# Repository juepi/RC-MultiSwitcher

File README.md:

# RC-MultiSwitcher
Hard- and software project to handle several RC (PWM) Servo In- and outputs as well as switched Outputs for LEDs and other loads.

## Purpose
My intention for this project was to be able to use a single RC channel for multiple purposes, like switching headlights, flashing lights, siren etc on my RC model. To be more flexible, the board provides 4 PWM servo inputs as well as 4 outputs, which can be used simultaneously. It additionally supports 6 N-channel MOSFET outputs, supporting an optional free-wheeling diode for inductive loads on every output.

## Requirements
Whilst the program has been tested and runs on an Nano 3.0 clone, you may want to use something stronger like a [Teensy 3.1+ board](https://www.pjrc.com/teensy/teensy31.html) for this. The Nano causes some jitter on the servo outputs, i assume due to the interrupts used to measure the PWM signal of the 2 servo input channels interfering with the servo library code.  
If you choose a different microcontroller, my recommendation is to make sure that it is 5V tolerant on the digital inputs (just to be sure). Also remenber that you'll require inputs that support interrupts for decoding the receivers PWM signals.

## Status
This is work in progress, the current code is a POC on decoding the 2 RC channels along with servo output. Still much work to do adding the functionality i want and also a PCB to hook things up to.  
Some documentation available in comments which should help you get things up and running.  
**Update 2022-02-08:** Implemented support for Teensy 3.1/3.2 boards, Servo output jitter is history now!  
**Update 2022-02-11:** Added KiCAD project with schematic and layout for Teensy 3.1+ based MCU. KiCAD project is finished so far, will add gerber data as soon as i've finished the first order at JLCPCB.  
**Update 2022-02-14:** KiCAD project finished after some minor layout improvements. Added gerber, drilling, placement files as well as BoM in "production" subfolder.  
**Update 2022-02-24:** Implemented minor changes on PCB (v1.1): added possibility to provide power via 2pin JST XH plug; added solder-pad to short-circuit fuse (use with caution!); updated manufacturing files  
**Updated 2022-03-04:** Ordered PCB just arrived (v1.0) and works perfectly well! Not yet tested: high power load and PWM output on MOSFET switches.  

## Usage

have fun,  
Juergen

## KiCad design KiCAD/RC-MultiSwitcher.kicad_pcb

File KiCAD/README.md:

# RC-MultiSwitcher
Hardware part of the project. Designed using KiCAD6, SMT parts used from the [JLCPCB parts list](https://jlcpcb.com/parts) to allow pre-assembling all the SMT parts.

## Purpose
Provide power to teensy MCU from BEC (up to 7.2V, Servo input 1) using LDO regulator provide hardware connections for Servo in- and outputs as wells as 6 N-channel MOSFET switched outputs (all 6 support PWM). The PCB has a 5A polyfuse installed at the power input to avoid overload (however, you will still have to make sure that you do not overload your BEC).

## Requirements
The [KiCAD Teensy libraries](https://github.com/XenGi/teensy_library) have been used for this board, they are included in the lib folder. The footprint has been slightly adopted to include only the main 2 pin-rows of the Teensy.

## Status
Schematic and layout finished, manufacturing data for [jlcpcb.com](https://jlcpcb.com/) added in "production" subfolder. 

## Changelog

### v1.1
- Added optional JST XH 2pin Power Input connector
- Added possibility to short circuit polyfuse with solder jumper on bottom side (use at your own risk!)
- updated manufacturing data
- Updated Net names of Switched Outputs to match code (SW0..SW5)

### v1.0
- Minor layout improvements
- changed C1 to different part with lower MOQ
- published manufacturing data

have fun,  
Juergen

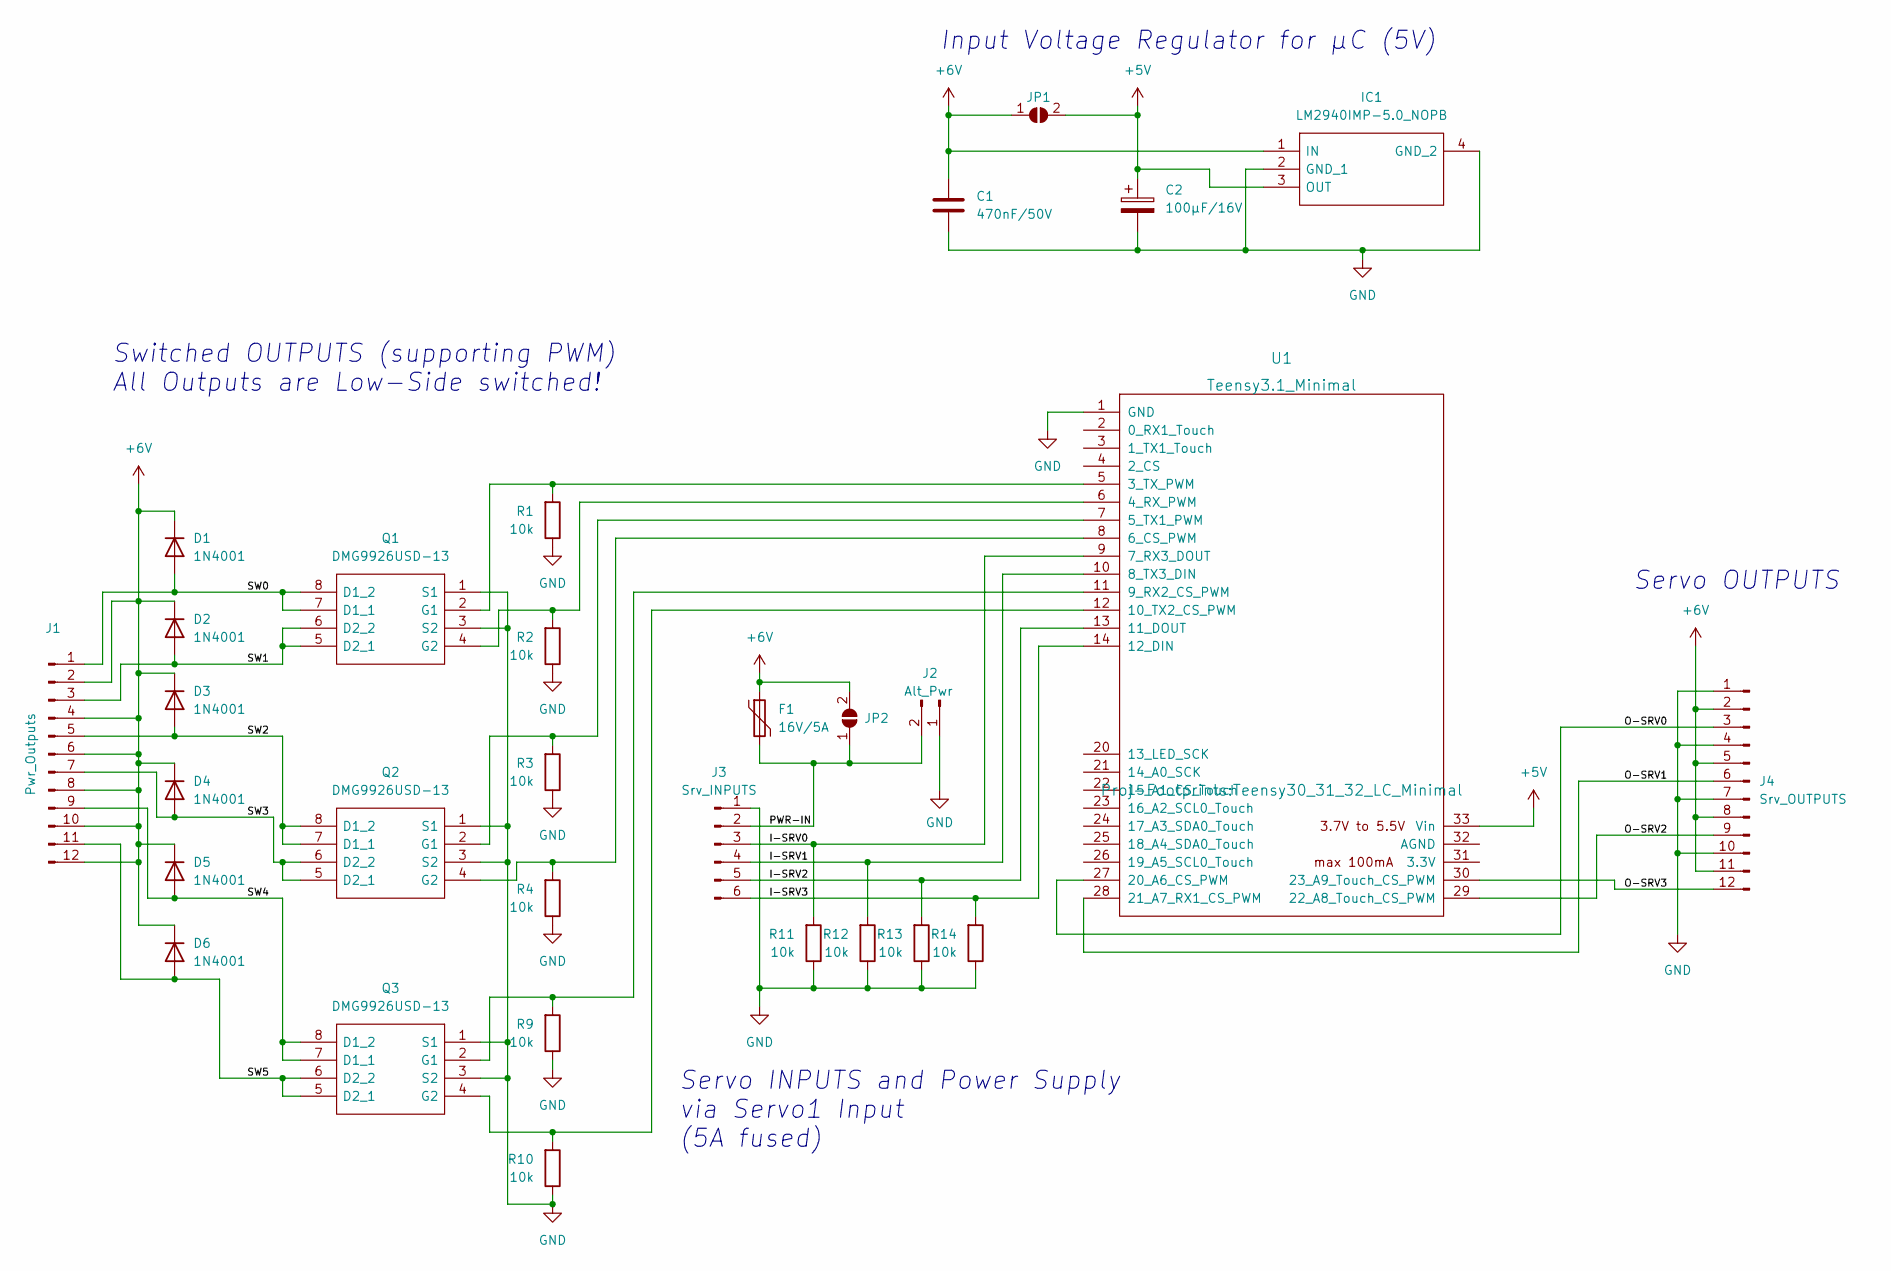
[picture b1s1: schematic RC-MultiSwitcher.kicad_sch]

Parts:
C1: 470nF/50V; C_0603_1608Metric; LCSC C77572
C2: 100µF/16V; CP_EIA-7343-31_Kemet-D; LCSC C171666
D1, D2, D3, D4, D5, D6: 1N4001; D_DO-41_SOD81_P2.54mm_Vertical_AnodeUp; LCSC DNP
F1: 16V/5A; Fuse_1812_4532Metric; LCSC C55996
IC1: LM2940IMP-5.0_NOPB; SOT230P700X180-4N; Manufacturer_Part_Number LM2940IMP-5.0/NOPB; LCSC C13991
J1: Pwr_Outputs; PinHeader_1x12_P2.54mm_Vertical; LCSC DNP
J2: Alt_Pwr; JST_XH_B2B-XH-A_1x02_P2.50mm_Vertical; LCSC DNP
J3: Srv_INPUTS; PinHeader_1x06_P2.54mm_Vertical; LCSC DNP
J4: Srv_OUTPUTS; PinHeader_1x12_P2.54mm_Vertical; LCSC DNP
JP1, JP2: SolderJumper-2_P1.3mm_Open_Pad1.0x1.5mm
Q1, Q2, Q3: DMG9926USD-13; SOIC127P600X175-8N; Manufacturer_Part_Number DMG9926USD-13; LCSC C154896
R1, R2, R3, R4, R9, R10, R11, R12, R13, R14: 10k; R_0402_1005Metric; LCSC C25744
U1: Teensy3.1_Minimal; Teensy30_31_32_LC_Minimal

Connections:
+5V: C2.1, IC1.3 (OUT), JP1.2 (B), U1.33 (Vin)
+6V: C1.1, D1.1 (K), D2.1 (K), D3.1 (K), D4.1 (K), D5.1 (K), D6.1 (K), F1.1, IC1.1 (IN), J1.2, J1.4, J1.6, J1.8, J1.10, J1.12, J4.2, J4.5, J4.8, J4.11, JP1.1 (A), JP2.2 (B)
/I-SRV0: J3.3, R11.2, U1.9 (7_RX3_DOUT)
/I-SRV1: J3.4, R12.2, U1.10 (8_TX3_DIN)
/I-SRV2: J3.5, R13.2, U1.13 (11_DOUT)
/I-SRV3: J3.6, R14.2, U1.14 (12_DIN)
/O-SRV0: J4.3, U1.27 (20_A6_CS_PWM)
/O-SRV1: J4.6, U1.28 (21_A7_RX1_CS_PWM)
/O-SRV2: J4.9, U1.29 (22_A8_Touch_CS_PWM)
/O-SRV3: J4.12, U1.30 (23_A9_Touch_CS_PWM)
/PWR-IN: F1.2, J2.2, J3.2, JP2.1 (A)
/SW0: D1.2 (A), J1.1, Q1.7 (D1_1), Q1.8 (D1_2)
/SW1: D2.2 (A), J1.3, Q1.5 (D2_1), Q1.6 (D2_2)
/SW2: D3.2 (A), J1.5, Q2.7 (D1_1), Q2.8 (D1_2)
/SW3: D4.2 (A), J1.7, Q2.5 (D2_1), Q2.6 (D2_2)
/SW4: D5.2 (A), J1.9, Q3.7 (D1_1), Q3.8 (D1_2)
/SW5: D6.2 (A), J1.11, Q3.5 (D2_1), Q3.6 (D2_2)
GND: C1.2, C2.2, IC1.2 (GND_1), IC1.4 (GND_2), J2.1, J3.1, J4.1, J4.4, J4.7, J4.10, Q1.1 (S1), Q1.3 (S2), Q2.1 (S1), Q2.3 (S2), Q3.1 (S1), Q3.3 (S2), R1.1, R2.1, R3.1, R4.1, R9.1, R10.1, R11.1, R12.1, R13.1, R14.1, U1.1 (GND)
unnamed: Q1.2 (G1), R1.2, U1.5 (3_TX_PWM)
unnamed: Q1.4 (G2), R2.2, U1.6 (4_RX_PWM)
unnamed: Q2.2 (G1), R3.2, U1.7 (5_TX1_PWM)
unnamed: Q2.4 (G2), R4.2, U1.8 (6_CS_PWM)
unnamed: Q3.2 (G1), R9.2, U1.11 (9_RX2_CS_PWM)
unnamed: Q3.4 (G2), R10.2, U1.12 (10_TX2_CS_PWM)

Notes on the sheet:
Servo INPUTS and Power Supply via Servo1 Input (5A fused)
Switched OUTPUTS (supporting PWM) All Outputs are Low-Side switched!
Input Voltage Regulator for µC (5V)
Servo OUTPUTS

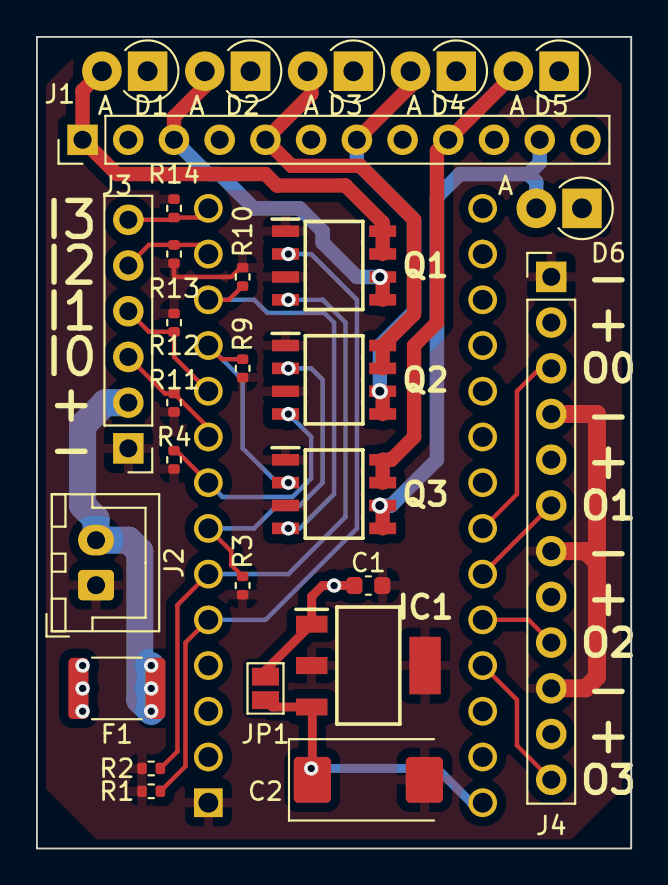
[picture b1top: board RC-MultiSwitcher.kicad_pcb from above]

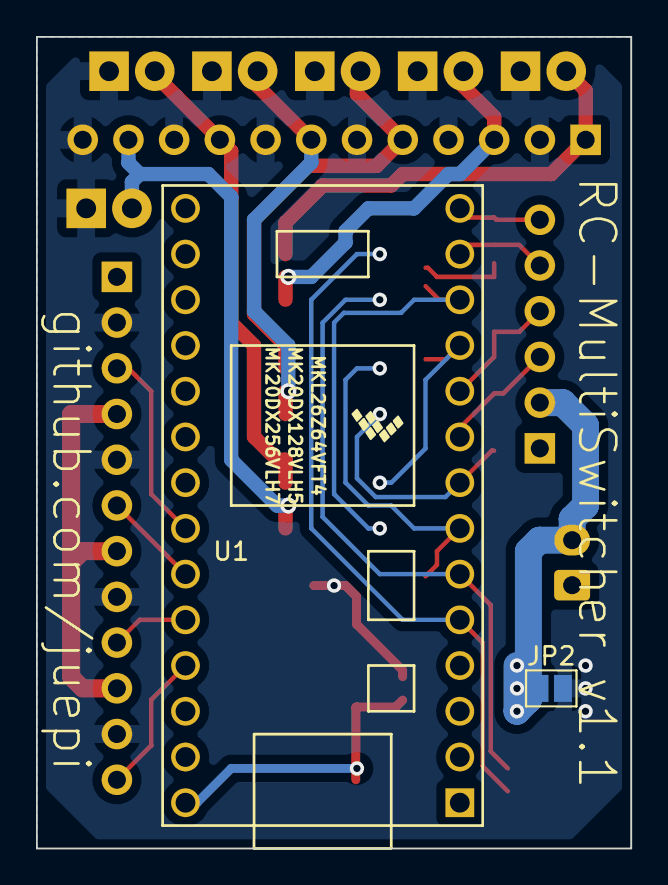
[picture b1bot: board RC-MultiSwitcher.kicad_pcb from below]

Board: 2 copper layers, 33.0 x 45.1 mm, 30 parts (2 on the bottom side), 24 nets.

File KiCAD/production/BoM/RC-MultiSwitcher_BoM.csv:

Comment,Designator,Footprint,LCSC part number
"470nF/50V","C1","Capacitor_SMD:C_0603_1608Metric","C77572"
"100µF/16V","C2","Capacitor_Tantalum_SMD:CP_EIA-7343-31_Kemet-D","C171666"
"16V/5A","F1","Fuse:Fuse_1812_4532Metric","C55996"
"LM2940IMP-5.0_NOPB","IC1","Proj-Footprints:SOT230P700X180-4N","C13991"
"DMG9926USD-13","Q1,Q2,Q3","Proj-Footprints:SOIC127P600X175-8N","C154896"
"10k","R1,R2,R3,R4,R9,R10,R11,R12,R13,R14","Resistor_SMD:R_0402_1005Metric","C25744"

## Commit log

2022-01-28 first poc
2022-02-08 added teensy support; v1.0.1
2022-02-08 formatting change
2022-02-10 updated directory structure
2022-02-11 added KiCAD schematic and layout; minor code updates
2022-02-11 updated readmes
2022-02-14 minor layout improvements; added manufacturing data
2022-02-14 updated main readme
2022-02-14 added pcb usage infos
2022-02-14 readme update
2022-02-24 minor update to PCB
2022-03-03 major code updates
2022-03-03 added option to set PWM frequency for SW outputs
2022-03-04 code updated after testing with PCB HW v1.0
2022-03-04 readme formatting
2022-03-07 changed SW pinout to be able to use high frequency PWM for pump motor
2022-03-09 added SW-testign mode
2022-03-14 added iBUS support
2022-03-15 readme/comment updates
2022-03-15 testing PWM Switches - buggy
2022-03-15 minor code tweaking for PWM switch outputs
2022-03-26 adopted in-out-handling for personal use case
2022-03-31 personal change - added foglights
2022-04-06 updated code readme
